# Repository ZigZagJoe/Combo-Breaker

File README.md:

# Combo-Breaker
Combination Breakout board for MacSE/30 / IIsi: VGA + DB15 + Ethernet (Bolle or SEthernet)

CURRENT REVISION DOES NOT WORK WITH BOLLE RISER. DO NOT USE WITH BOLLE RISER WITHOUT REMOVING PINS 4,5

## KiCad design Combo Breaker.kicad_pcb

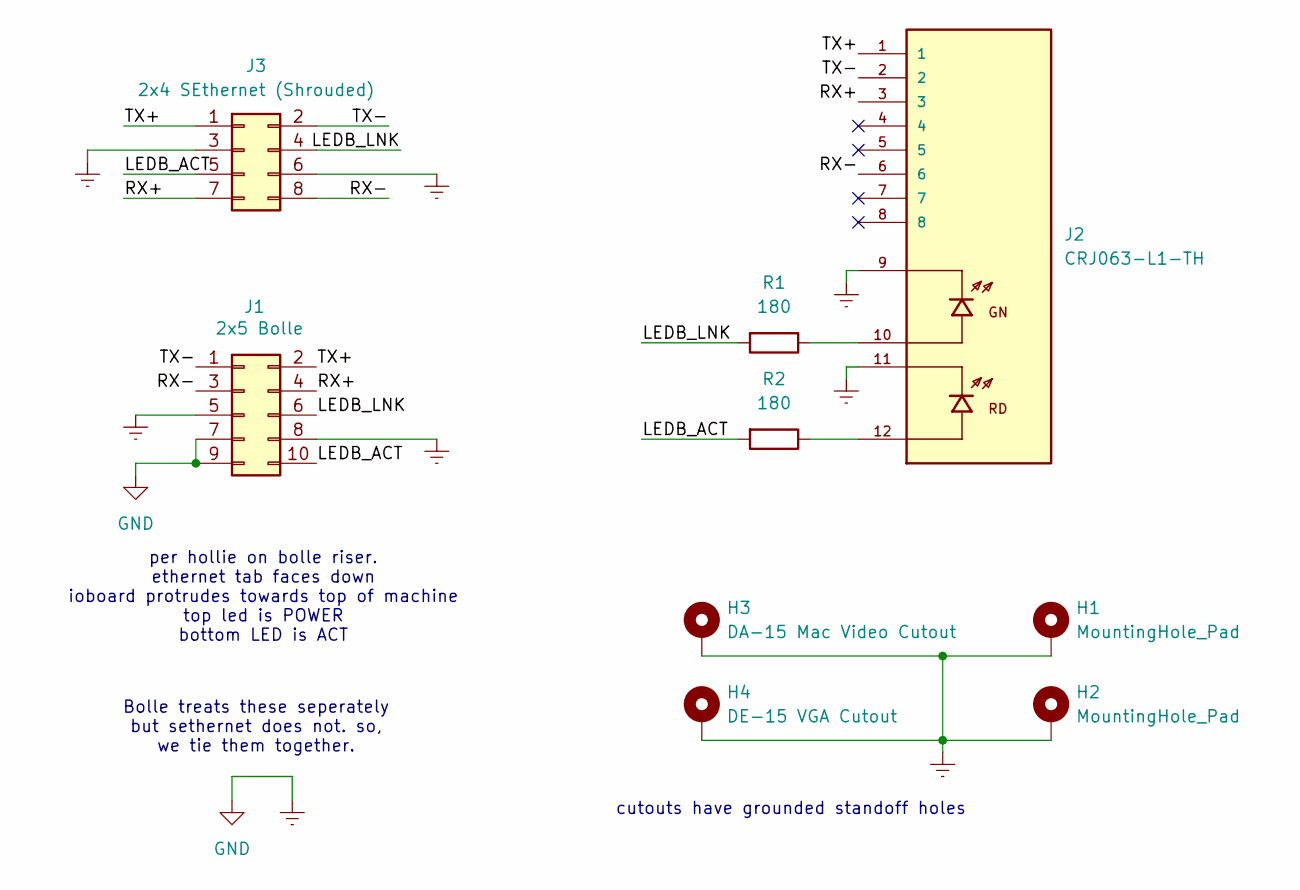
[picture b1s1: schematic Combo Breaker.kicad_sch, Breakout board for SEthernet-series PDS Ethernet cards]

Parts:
H1, H2: MountingHole_Pad; MountingHole_3.5mm_Pad; Digikey 9774025360R
H3: DA-15 Mac Video Cutout; DA-15 Cutout
H4: DE-15 VGA Cutout; DE-15 Cutout
J1: 2x5 Bolle; PinHeader_2x05_P2.54mm_Vertical
J2: CRJ063-L1-TH; CUI_CRJ063-L1-TH; PARTREV 1.0; Digikey CRJ063-L1-TH
J3: 2x4 SEthernet (Shrouded); IDC-Header_2x04_P2.54mm_Vertical; Digikey 302-S101
R1, R2: 180; R_Axial_DIN0207_L6.3mm_D2.5mm_P10.16mm_Horizontal; Digikey CF18JT180R

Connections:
/LEDB_ACT: J1.10, J3.5, R2.2
/LEDB_LNK: J1.6, J3.4, R1.2
/RX+: J1.4, J2.3, J3.7
/RX-: J1.3, J2.6, J3.8
/TX+: J1.2, J2.1, J3.1
/TX-: J1.1, J2.2, J3.2
Earth: H1.1, H2.1, H3.1, H4.1, J1.5, J1.7, J1.8, J1.9, J2.9, J2.11, J3.3, J3.6
unnamed: J2.10, R1.1
unnamed: J2.12, R2.1

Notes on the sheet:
per hollie on bolle riser. ethernet tab faces down ioboard protrudes towards top of machine top led is POWER bottom LED is ACT
cutouts have grounded standoff holes
Bolle treats these seperately but sethernet does not. so, we tie them together.

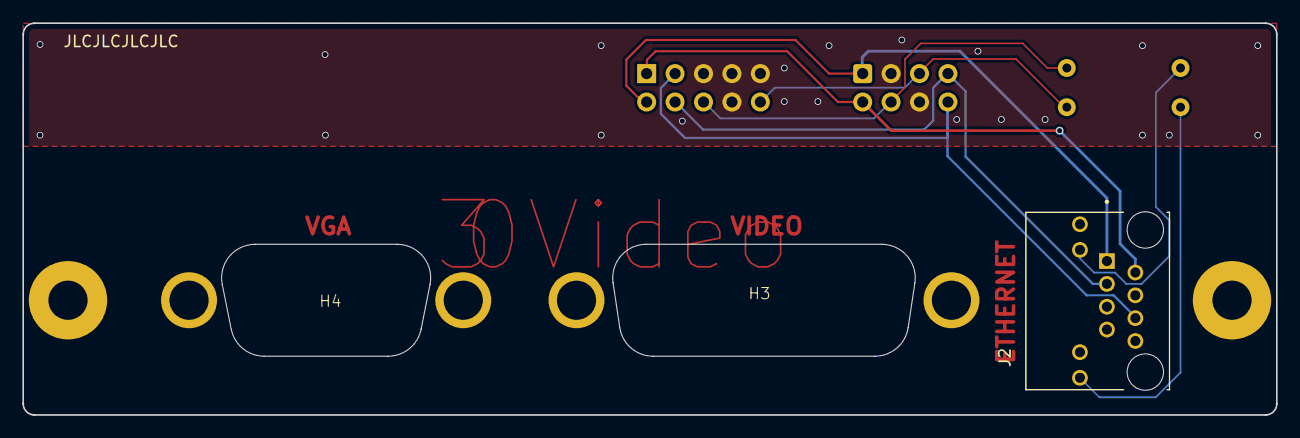
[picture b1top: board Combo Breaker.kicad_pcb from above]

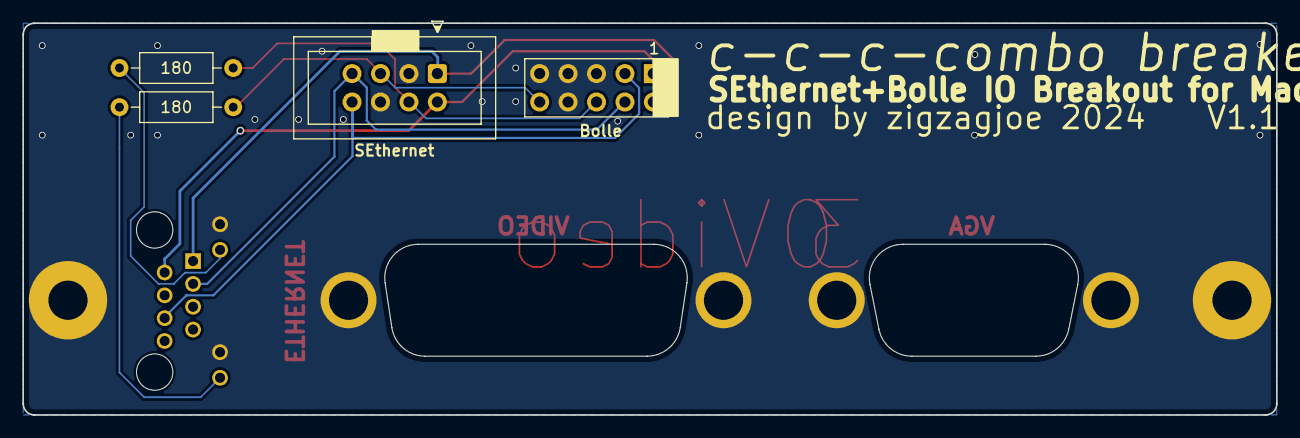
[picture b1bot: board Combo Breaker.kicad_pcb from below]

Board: 2 copper layers, 112.0 x 35.0 mm, 9 parts (4 on the bottom side), 9 nets.

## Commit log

2025-02-05 Does not work with Bolle riser
